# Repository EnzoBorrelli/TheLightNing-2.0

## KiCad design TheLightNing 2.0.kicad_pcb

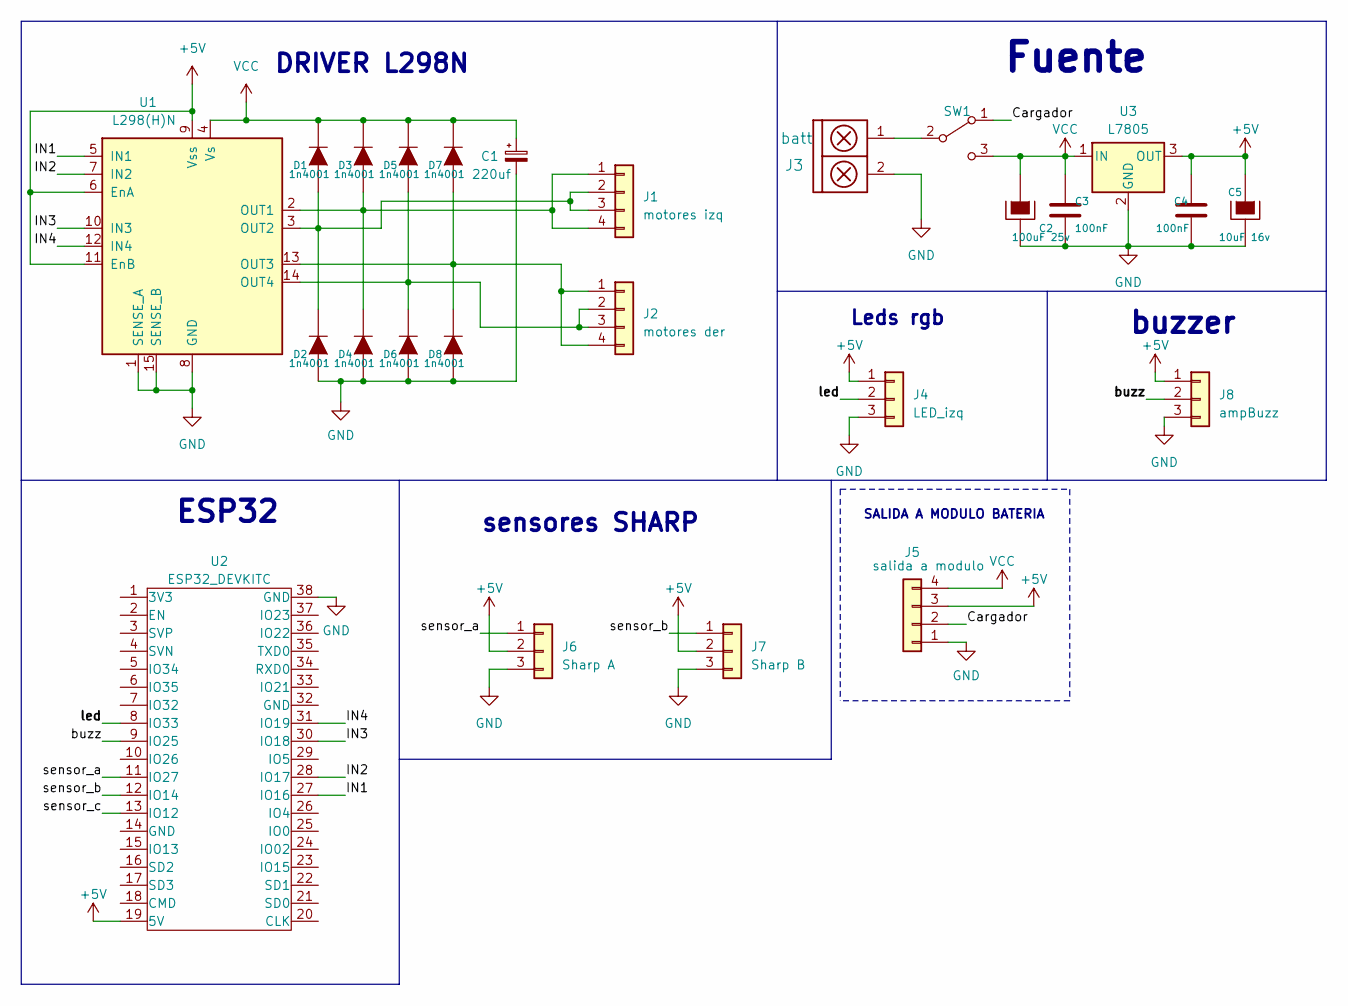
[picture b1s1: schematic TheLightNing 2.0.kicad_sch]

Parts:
C1: 220uf; CAP_ELEC_5x11mm
C2: 100uF 25v; CAP_ELEC_5x11mm
C3, C4: 100nF; CAP_0.1
C5: 10uF 16v; CAP_ELEC_5x11mm
D1, D2, D3, D4, D5, D6, D7, D8: 1n4001; DO-41
J1: motores izq; pin_strip_4
J2: motores der; pin_strip_4
J3: batt; Pin_Header_2
J4: LED_izq; Pin_Strip_3
J5: salida a modulo; pin_strip_4
J6: Sharp A; Pin_Strip_3
J7: Sharp B; Pin_Strip_3
J8: ampBuzz; Pin_Strip_3
SW1: SW_SPDT; Pin_Strip_3
U1: L298(H)N; TO-220-15_P2.54x2.54mm_StaggerEven_Lead4.58mm_Vertical
U2: ESP32_DEVKITC; ESP32S
U3: L7805; TO-220

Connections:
+5V: C4.1, C5.1, J4.1, J5.3, J6.2, J7.2, J8.1, U1.6 (EnA), U1.9 (Vss), U1.11 (EnB), U2.19 (5V), U3.3 (OUT)
/Cargador: J5.2, SW1.1 (A)
/IN1: U1.5 (IN1), U2.27 (IO16)
/IN2: U1.7 (IN2), U2.28 (IO17)
/IN3: U1.10 (IN3), U2.30 (IO18)
/IN4: U1.12 (IN4), U2.31 (IO19)
/buzz: J8.2, U2.9 (IO25)
/led: J4.2, U2.8 (IO33)
/sensor_a: J6.1, U2.11 (IO27)
/sensor_b: J7.1, U2.12 (IO14)
/sensor_c: U2.13 (IO12)
GND: C1.2, C2.2, C3.2, C4.2, C5.2, D2.1 (A), D4.1 (A), D6.1 (A), D8.1 (A), J3.2, J4.3, J5.1, J6.3, J7.3, J8.3, U1.1 (SENSE_A), U1.8 (GND), U1.15 (SENSE_B), U2.38 (GND), U3.2 (GND)
unnamed: D1.1 (A), D2.2 (K), J1.2, J1.3, U1.3 (OUT2)
unnamed: D3.1 (A), D4.2 (K), J1.1, J1.4, U1.2 (OUT1)
unnamed: D5.1 (A), D6.2 (K), J2.2, J2.3, U1.14 (OUT4)
unnamed: D7.1 (A), D8.2 (K), J2.1, J2.4, U1.13 (OUT3)
unnamed: J3.1, SW1.2 (B)
VCC: C1.1, C2.1, C3.1, D1.2 (K), D3.2 (K), D5.2 (K), D7.2 (K), J5.4, SW1.3 (C), U1.4 (Vs), U3.1 (IN)

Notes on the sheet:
SALIDA A MODULO BATERIA
Fuente
sensores SHARP
buzzer
DRIVER L298N
ESP32
Leds rgb

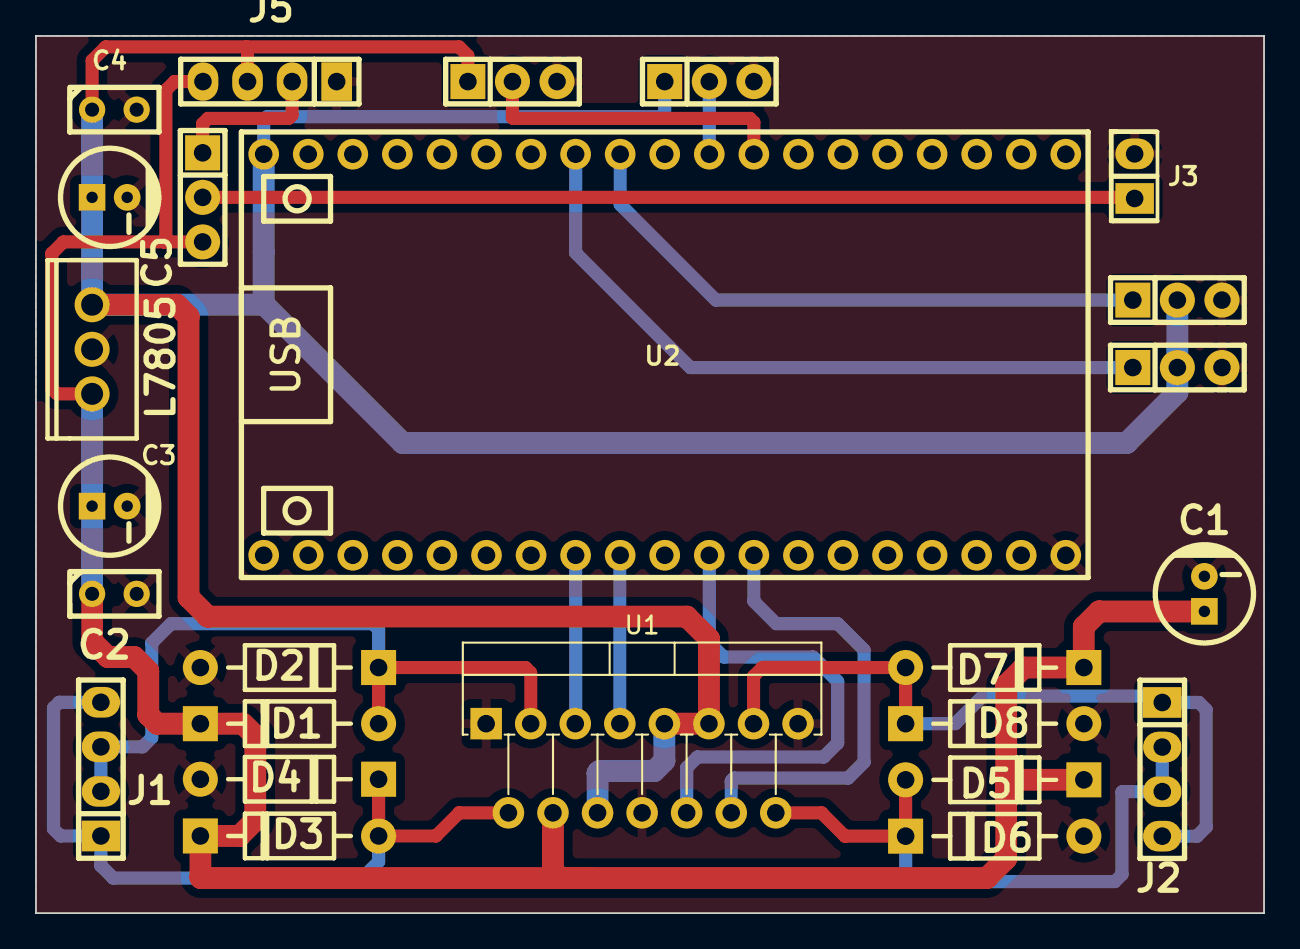
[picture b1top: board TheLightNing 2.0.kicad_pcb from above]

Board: 2 copper layers, 70.0 x 50.0 mm, 25 parts (0 on the bottom side), 17 nets.

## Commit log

2023-06-08 buzzer agregado
2023-06-28 re-made
2023-09-26 rework
2023-09-27 sharps
2023-09-28 final version 1.5
2023-09-28 pin connection fixed
2023-09-28 reorganizacion
2023-09-29 code v1
